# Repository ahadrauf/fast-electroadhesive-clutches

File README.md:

# Optimizing Electroadhesive Clutches for Sub-Millisecond Response Times

Robots can use fast, controllable clutches for dynamic load bearing and programmable stiffness. Electroadhesion (EA) is a technology that offers these capabilities in an ultra-compact and flexible form factor, but its inconsistent dynamics limit real-world use.

To address this uncertainty, we built an analytical electromechanical dynamics model for electroadhesion, factoring in contact mechanics between the dielectric and substrate, polarization dynamics, and the drive circuitry’s rise and fall times. Dual optimization over both the electrical and contact mechanics allows us to improve clutch dynamics while maintaining high force output. The fastest clutches in our study can repeatably:
 * Engage in <15 μs (10x faster than prior work)
 * Release in <1 ms (17x faster than prior work)
 * Bandwidth >10 kHz (10x higher than prior work)
 * Recover after slip in <4 ms (roughly 5x faster than prior work)

In the main paper (open access link [here](https://arxiv.org/abs/2412.16803), journal link [here](https://www.sciencedirect.com/science/article/abs/pii/S235243162500094X)), we compare our model’s predictions for electroadhesive engagement and release times to experimental results across four operating and geometric design parameters with good conformity. We find that higher drive frequencies and narrower substrate aspect ratios enable significantly faster actuator response times, in particular improving release times.

We also compare our model’s predictions to broader experimental trends in prior literature, in particular explaining why larger substrate widths and lengths, lower voltages, and intermediate dielectric thicknesses result in larger release times. To our knowledge, this is the first analytical model for electroadhesion explaining these experimental trends.

## Methods (Modeling)

Our analytical model for electroadhesion dynamics included, from left to right in the equation above, the contact mechanics force between the dielectric and substrate, squeeze film damping, the electroadhesive attractive force, the dielectric's weight, and any external applied loads.

Using our free body diagram, we simulated how these parameters affect electroadhesion’s quasistatic and dynamic performance, and we validated these simulations via both finite element analysis and experimental testing.  

## Methods (Experimental)
To measure the engagement and release times of electroadhesive clutches down to the tens of microseconds, we built a custom tensile testing setup, as shown below.

We also designed a custom high voltage DC-DC converter and shift register circuit, the schematic of which is shown below.

## Navigating This Repository
Each of the figures in the ``scripts/`` folder are named according to the paper figure they generate. The experimental data that produced these figures are stored in the ``data/`` folder (mostly comprising log files for the ~400 tensile testing experiments reported on in this paper).

The code to run a tensile test is located in ``scripts/run_tensile_test.py``. This script expects that the code in the ``teensy/`` folder has also been loaded onto both the Teensy microcontrollers controlling the tensile testing setup and the shift register PCB.

CAD files for the tensile testing setup are located in the ``cad/`` folder, and KiCAD PCB files for the Microchip HV 507 shift register and power electronics circuit are located in the ``pcb/`` folder.

## Bibliography
[1] A. M. Rauf and S. Follmer, “Modeling the dynamics of sub-millisecond electroadhesive engagement and release times,” Extreme Mechanics Letters, vol. 79, p. 102382, Sept. 2025, doi: [10.1016/j.eml.2025.102382](https://doi.org/10.1016/j.eml.2025.102382). (Open Access arXiv link [here](https://arxiv.org/abs/2412.16803))

@article{Rauf_Follmer_2025, title={Modeling the dynamics of sub-millisecond electroadhesive engagement and release times}, volume={79}, rights={All rights reserved}, ISSN={2352-4316}, DOI={10.1016/j.eml.2025.102382}, abstractNote={Electroadhesive clutches are electrically controllable switchable adhesives commonly used in soft robots and haptic user interfaces. They can form strong bonds to a wide variety of surfaces at low power consumption. However, electroadhesive clutches in the literature engage to and release from substrates several orders of magnitude slower than a traditional electrostatic model would predict. Large release times, in particular, can limit electroadhesion’s usefulness in high-bandwidth applications. We develop a novel electromechanical model for electroadhesion, factoring in polarization dynamics, the drive circuitry’s rise and fall times, and contact mechanics between the dielectric and substrate. We show in simulation and experimentally how different design parameters affect the engagement and release times of centimeter-scale electroadhesive clutches to metallic substrates, and we find that the model accurately captures the magnitude and trends of our experimental results. In particular, we find that higher drive frequencies, narrower substrate aspect ratios, and faster drive circuitry output stages enable significantly faster release times. The fastest clutches have engagement times less than 15μs and release times less than 875μs, which are 10× and 17.1× faster, respectively, than the best times found in prior literature on centimeter-scale electroadhesive clutches.}, journal={Extreme Mechanics Letters}, author={Rauf, Ahad M. and Follmer, Sean}, year={2025}, month=sept, pages={102382} }

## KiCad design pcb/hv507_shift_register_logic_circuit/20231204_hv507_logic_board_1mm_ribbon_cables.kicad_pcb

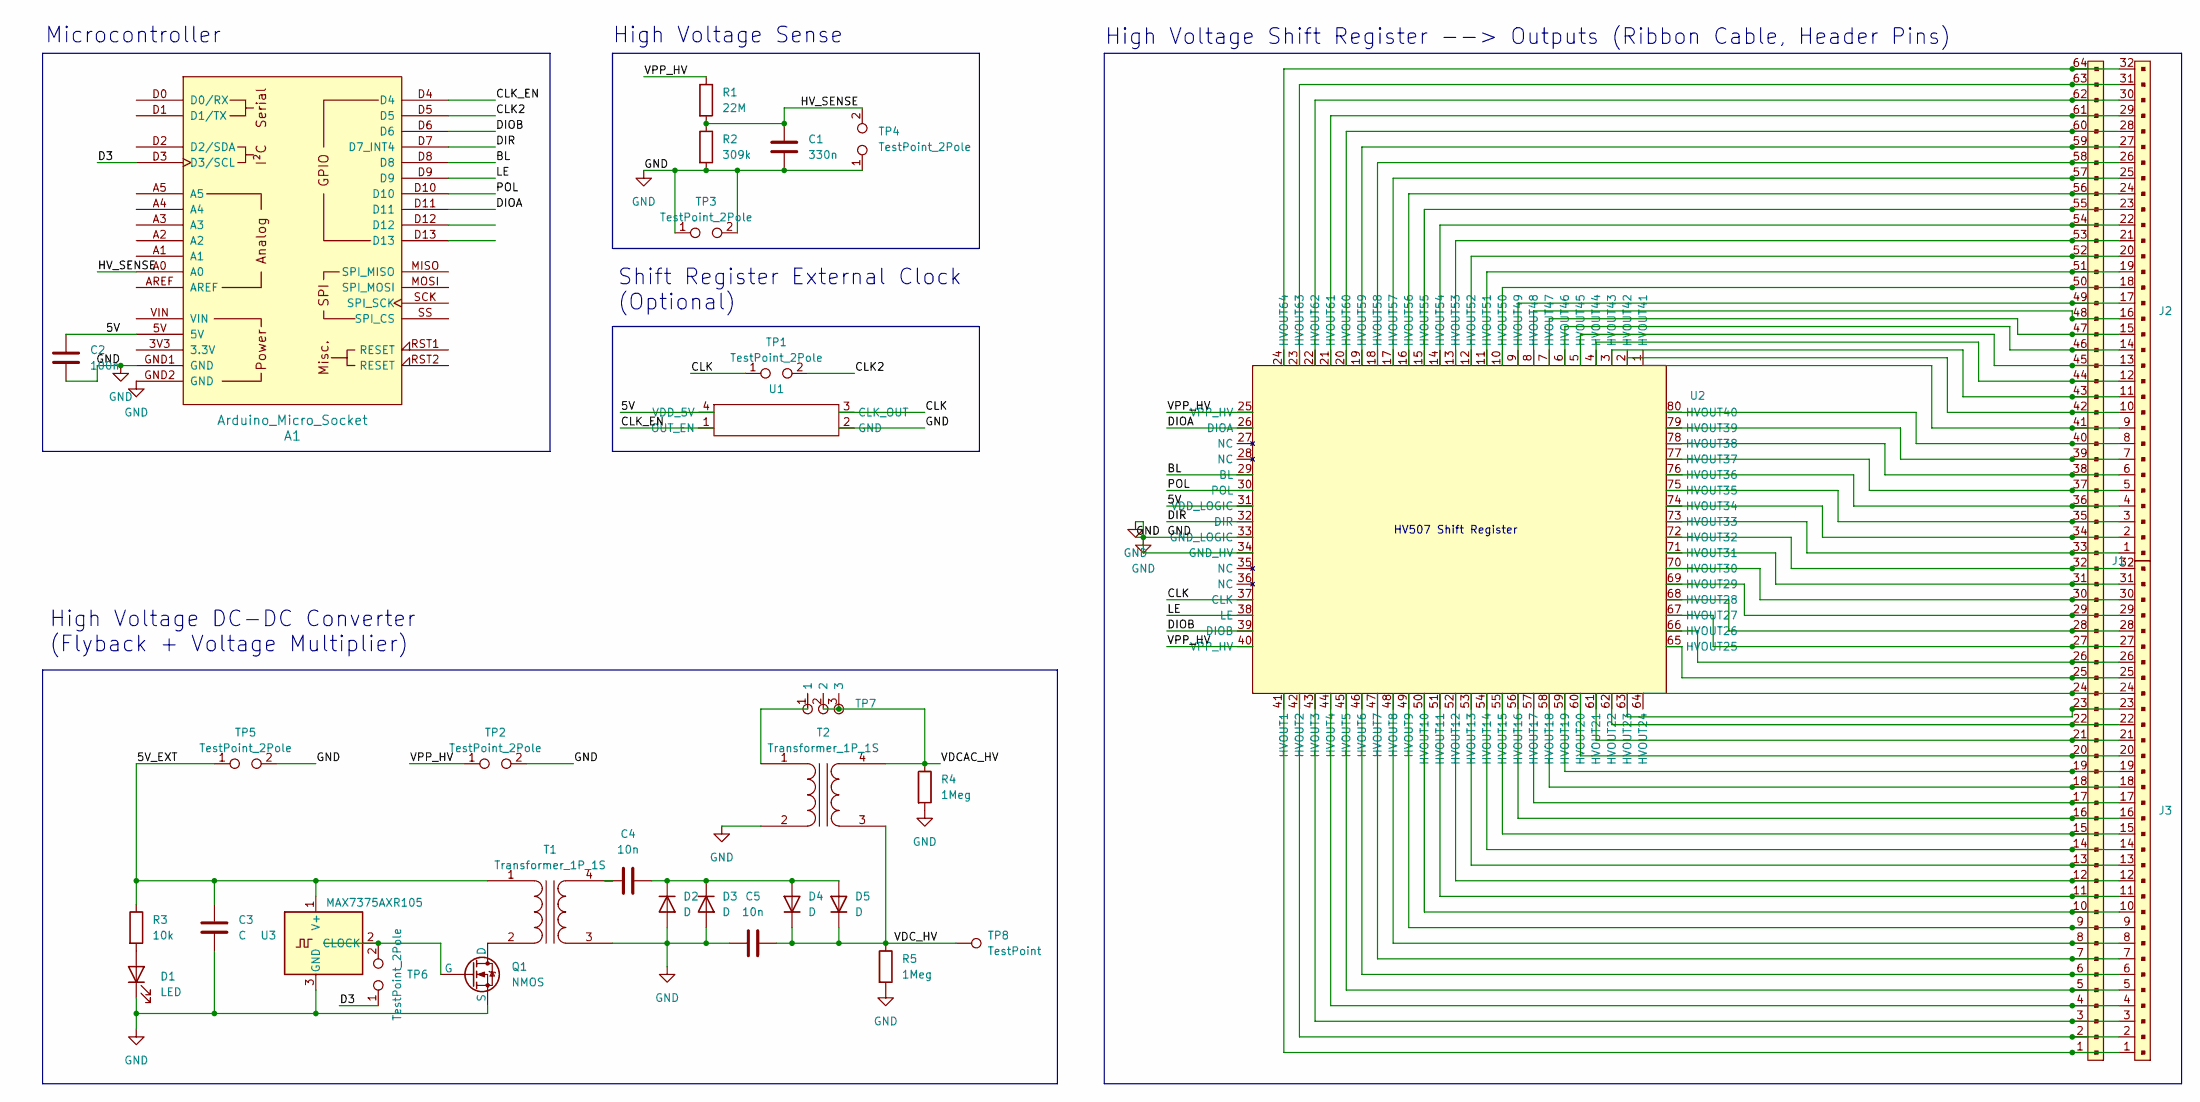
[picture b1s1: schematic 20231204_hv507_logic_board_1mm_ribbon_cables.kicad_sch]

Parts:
A1: Arduino_Micro_Socket; Arduino_Micro_Socket_ProbeRow
C1: 330n; C_0603_1608Metric_Pad1.08x0.95mm_HandSolder
C2: 100n; C_0603_1608Metric_Pad1.08x0.95mm_HandSolder
C3: C; C_0603_1608Metric_Pad1.08x0.95mm_HandSolder
C4, C5: 10n; C_0603_1608Metric_Pad1.08x0.95mm_HandSolder
D1: LED; C_0603_1608Metric_Pad1.08x0.95mm_HandSolder
D2, D4: D; TO-220-2_Vertical
D3, D5: D; D_SOD-523
J1: PinHeader_32x2_P2.54mm_Vertical2
J2, J3: CF25321D0R0-10-NH
Q1: NMOS; SOT-883
R1: 22M; R_0805_2012Metric_Pad1.20x1.40mm_HandSolder
R2: 309k; R_0805_2012Metric_Pad1.20x1.40mm_HandSolder
R3: 10k; R_0805_2012Metric_Pad1.20x1.40mm_HandSolder
R4, R5: 1Meg; R_0805_2012Metric_Pad1.20x1.40mm_HandSolder
T1: Transformer_1P_1S; UA7868-AE Coupled Inductor
T2: Transformer_1P_1S; LPD5030V 1-1 Coupled Inductor
TP1, TP2, TP3, TP4, TP5, TP6: TestPoint_2Pole; PinHeader_1x02_P2.54mm_Vertical
TP7: PinHeader_1x03_P2.54mm_Vertical
TP8: TestPoint; PinHeader_1x01_P2.54mm_Vertical
U1: SMD-4_3.2x2.5
U2: PQFP-80_14x20mm_P0.8mm
U3: MAX7375AXR105; SOT-323_SC-70

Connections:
/5V: A1.5V, C2.1, U1.4 (VDD_5V), U2.31 (VDD_LOGIC)
/5V_EXT: C3.2, R3.1, T1.1 (AA), TP5.1, U3.1 (V+)
/BL: A1.D8, U2.29 (BL)
/CLK: TP1.1, U1.3 (CLK_OUT), U2.37 (CLK)
/CLK2: A1.D5, TP1.2
/CLK_EN: A1.D4, U1.1 (OUT_EN)
/D3: A1.D3 (D3/SCL), TP6.1
/DIOA: A1.D11, U2.26 (DIOA)
/DIOB: A1.D6, U2.39 (DIOB)
/DIR: A1.D7 (D7_INT4), U2.32 (DIR)
/HV_SENSE: A1.A0, C1.1, R1.2, R2.1, TP4.2
/LE: A1.D9, U2.38 (LE)
/POL: A1.D10, U2.30 (POL)
/VDCAC_HV: R4.1, T2.4 (SB), TP7.2, TP7.3
/VDC_HV: C5.2, D4.1 (K), D5.1 (K), R5.1, T2.3 (SA), TP8.1
/VPP_HV: R1.1, TP2.1, U2.25 (VPP_HV), U2.40 (VPP_HV)
GND: A1.GND1 (GND), A1.GND2 (GND), C1.2, C2.2, C3.1, C5.1, D1.1 (K), D2.2 (A), D3.2 (A), Q1.3 (S), R2.2, R4.2, R5.2, T1.3 (SA), T2.2 (AB), TP2.2, TP3.1, TP3.2, TP4.1, TP5.2, U1.2 (GND), U2.33 (GND_LOGIC), U2.34 (GND_HV), U3.3 (GND)
unnamed: D1.2 (A), R3.2
unnamed: C4.2, D2.1 (K), D3.1 (K), D4.2 (A), D5.2 (A)
unnamed: Q1.1 (D), T1.2 (AB)
unnamed: Q1.2 (G), TP6.2, U3.2 (CLOCK)
unnamed: C4.1, T1.4 (SB)
unnamed: T2.1 (AA), TP7.1
unnamed: J1.1, J3.1, U2.41 (HVOUT1)
unnamed: J1.2, J3.2, U2.42 (HVOUT2)
unnamed: J1.3, J3.3, U2.43 (HVOUT3)
unnamed: J1.4, J3.4, U2.44 (HVOUT4)
unnamed: J1.5, J3.5, U2.45 (HVOUT5)
unnamed: J1.6, J3.6, U2.46 (HVOUT6)
unnamed: J1.7, J3.7, U2.47 (HVOUT7)
unnamed: J1.8, J3.8, U2.48 (HVOUT8)
unnamed: J1.9, J3.9, U2.49 (HVOUT9)
unnamed: J1.10, J3.10, U2.50 (HVOUT10)
unnamed: J1.11, J3.11, U2.51 (HVOUT11)
unnamed: J1.12, J3.12, U2.52 (HVOUT12)
unnamed: J1.13, J3.13, U2.53 (HVOUT13)
unnamed: J1.14, J3.14, U2.54 (HVOUT14)
unnamed: J1.15, J3.15, U2.55 (HVOUT15)
unnamed: J1.16, J3.16, U2.56 (HVOUT16)
unnamed: J1.17, J3.17, U2.57 (HVOUT17)
unnamed: J1.18, J3.18, U2.58 (HVOUT18)
unnamed: J1.19, J3.19, U2.59 (HVOUT19)
unnamed: J1.20, J3.20, U2.60 (HVOUT20)
unnamed: J1.21, J3.21, U2.61 (HVOUT21)
unnamed: J1.22, J3.22, U2.62 (HVOUT22)
unnamed: J1.23, J3.23, U2.63 (HVOUT23)
unnamed: J1.24, J3.24, U2.64 (HVOUT24)
unnamed: J1.25, J3.25, U2.65 (HVOUT25)
unnamed: J1.26, J3.26, U2.66 (HVOUT26)
unnamed: J1.27, J3.27, U2.67 (HVOUT27)
unnamed: J1.28, J3.28, U2.68 (HVOUT28)
unnamed: J1.29, J3.29, U2.69 (HVOUT29)
unnamed: J1.30, J3.30, U2.70 (HVOUT30)
unnamed: J1.31, J3.31, U2.71 (HVOUT31)
unnamed: J1.32, J3.32, U2.72 (HVOUT32)
unnamed: J1.33, J2.1, U2.73 (HVOUT33)
unnamed: J1.34, J2.2, U2.74 (HVOUT34)
unnamed: J1.35, J2.3, U2.75 (HVOUT35)
unnamed: J1.36, J2.4, U2.76 (HVOUT36)
unnamed: J1.37, J2.5, U2.77 (HVOUT37)
unnamed: J1.38, J2.6, U2.78 (HVOUT38)
unnamed: J1.39, J2.7, U2.79 (HVOUT39)
unnamed: J1.40, J2.8, U2.80 (HVOUT40)
unnamed: J1.41, J2.9, U2.1 (HVOUT41)
unnamed: J1.42, J2.10, U2.2 (HVOUT42)
unnamed: J1.43, J2.11, U2.3 (HVOUT43)
unnamed: J1.44, J2.12, U2.4 (HVOUT44)
unnamed: J1.45, J2.13, U2.5 (HVOUT45)
unnamed: J1.46, J2.14, U2.6 (HVOUT46)
unnamed: J1.47, J2.15, U2.7 (HVOUT47)
unnamed: J1.48, J2.16, U2.8 (HVOUT48)
unnamed: J1.49, J2.17, U2.9 (HVOUT49)
unnamed: J1.50, J2.18, U2.10 (HVOUT50)
unnamed: J1.51, J2.19, U2.11 (HVOUT51)
unnamed: J1.52, J2.20, U2.12 (HVOUT52)
unnamed: J1.53, J2.21, U2.13 (HVOUT53)
unnamed: J1.54, J2.22, U2.14 (HVOUT54)
unnamed: J1.55, J2.23, U2.15 (HVOUT55)
unnamed: J1.56, J2.24, U2.16 (HVOUT56)
unnamed: J1.57, J2.25, U2.17 (HVOUT57)
unnamed: J1.58, J2.26, U2.18 (HVOUT58)
unnamed: J1.59, J2.27, U2.19 (HVOUT59)
unnamed: J1.60, J2.28, U2.20 (HVOUT60)
unnamed: J1.61, J2.29, U2.21 (HVOUT61)
unnamed: J1.62, J2.30, U2.22 (HVOUT62)
unnamed: J1.63, J2.31, U2.23 (HVOUT63)
unnamed: J1.64, J2.32, U2.24 (HVOUT64)

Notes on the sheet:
HV507 Shift Register
High Voltage DC-DC Converter (Flyback + Voltage Multiplier)
High Voltage Shift Register --> Outputs (Ribbon Cable, Header Pins)
Shift Register External Clock (Optional)
Microcontroller
High Voltage Sense

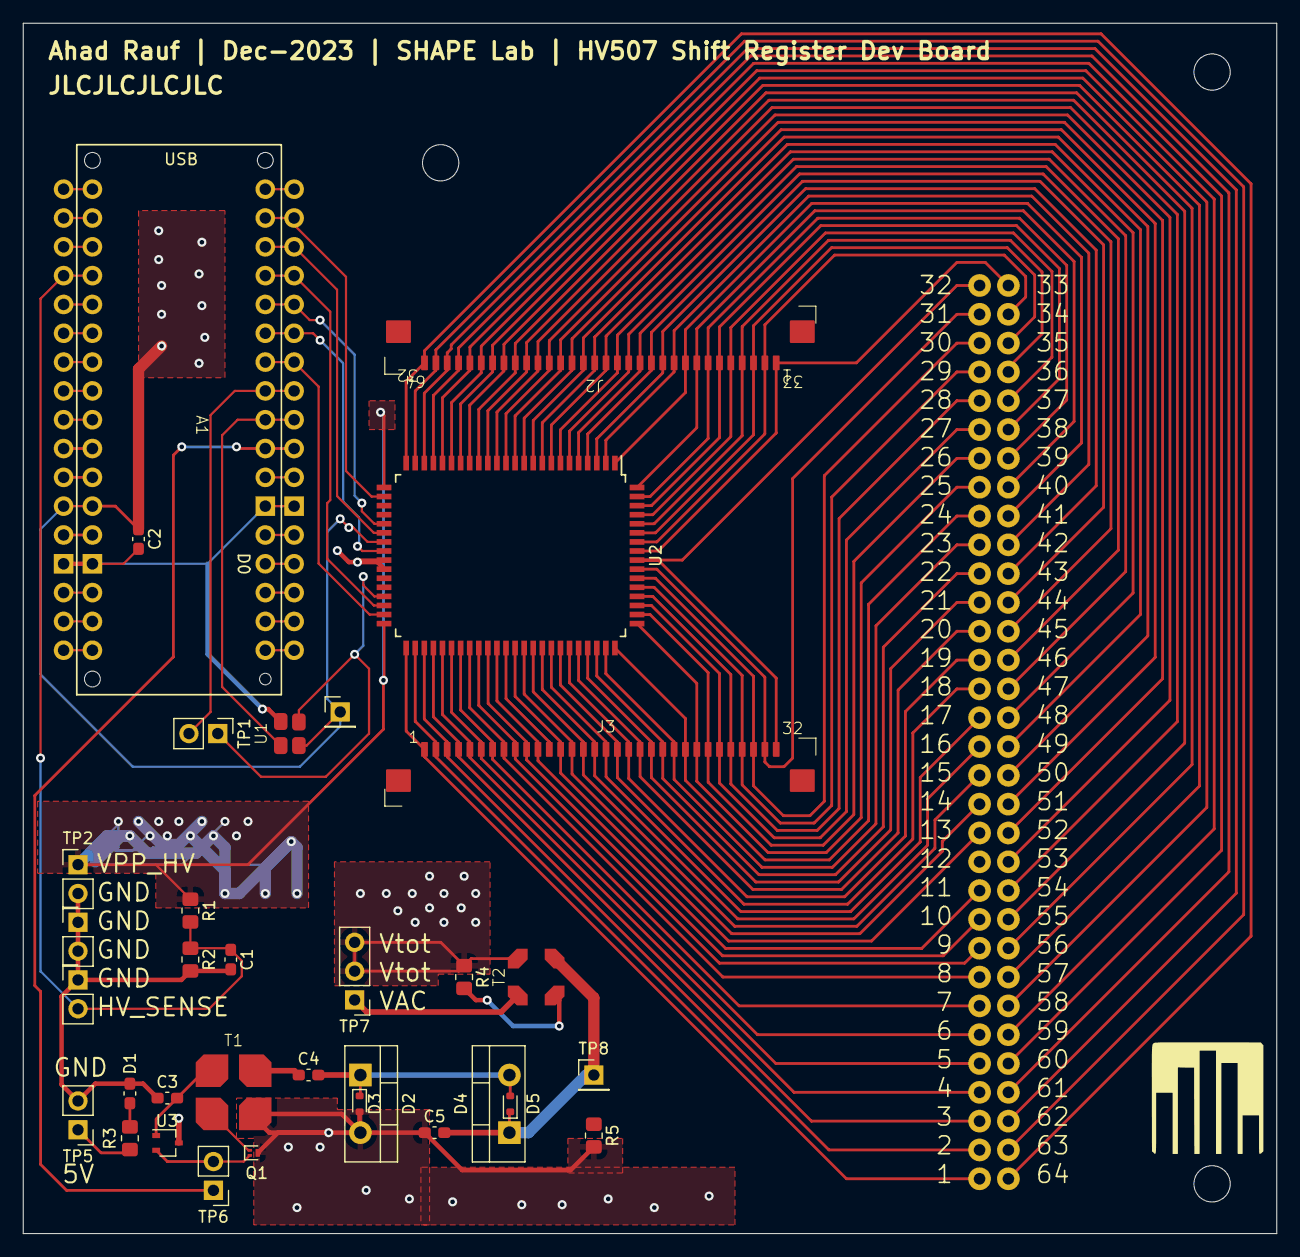
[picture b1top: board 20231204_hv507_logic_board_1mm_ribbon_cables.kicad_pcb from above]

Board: 2 copper layers, 110.5 x 106.7 mm, 33 parts (1 on the bottom side), 87 nets.

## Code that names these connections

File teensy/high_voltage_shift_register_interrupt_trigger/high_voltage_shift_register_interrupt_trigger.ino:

/***
Teensy 3.6 code for controlling the Microchip HV507 high voltage shift register

When the Teensy receives a trigger, it starts toggling the HV507 at a pre-defined bipolar
    square wave frequency. The code accepts two types of triggers: either the other Teensy
    triggers it by connecting the two Teensy's ground pins and linking the other Teensy's
    INTERRUPT_PIN to this Teensy's BUTTON_IN_PIN, or a push button can be connected between 
    this Teensy's BUTTON_IN_PIN and BUTTON_OUT_PIN (for other applications).
***/

#include "hv507.h"

const int PIN_CLK_EN = 24;
const int PIN_CLK = 25;
const int PIN_DIOB = 26;
const int PIN_DIR = 27;
const int PIN_BL = 28;
const int PIN_LE = 29;
const int PIN_POL = 30;
const int PIN_DIOA = 31;

const int LED_PIN = 13;
const int BUTTON_IN_PIN = 34;
const int BUTTON_OUT_PIN = 33;
const float FREQUENCY = 100;  // bipolar square wave drive frequency
const int DELAY = 1e6 / FREQUENCY / 2;
volatile int currIdx = 0;
bool forward = true;
volatile bool enabled = false;
volatile bool voltage_on_electrode1 = false;

HV507 hv507;
IntervalTimer timerBipolarSquareWave;

void setup() {
  pinMode(PIN_DIOB, INPUT);
  pinMode(BUTTON_OUT_PIN, OUTPUT);
  hv507.init(PIN_CLK, PIN_LE, PIN_DIOA, PIN_POL, PIN_BL, PIN_DIR);
  delay(100);
  hv507.loadArrayToRegister(0, 0, 0, 0);
  hv507.loadRegisterToOutput();
  pinMode(LED_PIN, OUTPUT);
  pinMode(BUTTON_IN_PIN, INPUT);
  digitalWrite(BUTTON_OUT_PIN, LOW);
  attachInterrupt(digitalPinToInterrupt(BUTTON_IN_PIN), hv507Toggle, CHANGE);
}

void loop() { }

void hv507Toggle() {
  if (digitalRead(BUTTON_IN_PIN) == HIGH) {
    timerBipolarSquareWave.end();
    digitalWrite(LED_PIN, HIGH);
    hv507.loadArrayToRegister(0x0100, 0x0000, 0x0000, 0x0000);
    hv507.loadRegisterToOutput();
    voltage_on_electrode1 = true;
    enabled = true;
    digitalWrite(BUTTON_OUT_PIN, HIGH);
    timerBipolarSquareWave.begin(hv507InvertOutputs, DELAY); // update time (us)
  } else {
    digitalWrite(LED_PIN, LOW);

    // Comment out for frequencies other than 0.1 Hz (so I'm logging voltages from the proper electrode)
    // timerBipolarSquareWave.end();
    // hv507.loadArrayToRegister(0x0000, 0x0000, 0x0000, 0x0000);
    // hv507.loadRegisterToOutput();
    // digitalWrite(BUTTON_OUT_PIN, LOW);
    // voltage_on_electrode1 = false;

    enabled = false;
  }
}

void hv507InvertOutputs() {
  if (voltage_on_electrode1 && enabled) {
    hv507.loadArrayToRegister(0x0000, 0x0000, 0x0000, 0x0080); // corresponds to pin 56 (56-48=8 --> plug 1000,0000 into https://www.rapidtables.com/convert/number/hex-to-binary.html?x=80)
    hv507.loadRegisterToOutput();
    voltage_on_electrode1 = false;
  } else if (!voltage_on_electrode1) {
    hv507.loadArrayToRegister(0x0100, 0x0000, 0x0000, 0x0000); // corresponds to pin 9
    hv507.loadRegisterToOutput();
    voltage_on_electrode1 = true;
  } else { // !voltage_on_electrode1 && !enabled (interrupt triggered to end voltage)
    hv507.loadArrayToRegister(0x0000, 0x0000, 0x0000, 0x0000); 
    hv507.loadRegisterToOutput();
    digitalWrite(BUTTON_OUT_PIN, LOW);
    voltage_on_electrode1 = false;
    timerBipolarSquareWave.end();
  }
}

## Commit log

2025-12-14 dissertation
2026-01-11 updated all files
2026-01-11 updated pcb folder structure
2026-01-12 Update title for clarity on response times
